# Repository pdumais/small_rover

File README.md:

# A remote controlled vehicle with a mechanical arm using ESP32 and a PS5 Dualsense controller
It's heavy, it's noisy, it's klonky and it looks like a rudimentary machine. That's exactly what I wanted to build.
This is work in progress, so no pictures of the final build yet

# Electronics
I chose to use 2 ESP32. It would have been easier to use just one, but I needed the memory of a esp32-s3 and the classic BT from the ESP32. So I'm using both. 
The ESP32 is the DualSense (PS5 controller) receiver. It handles the connection and incoming data from the Dualsense
and sends it on the i2c bus. This device will most probably end up handling other misc stuff too.

The esp32-s3 is main controller.
    - Controls the 4 motors
    - Controls servo for steering
    - Reads pulse count for each motors (RPM reading)
    - Controls the buzzer
    - Controls LED ring
  
# Choice of motors
I'm using 4 12v DC motors with a stall current of 7A with 4 DRV8871 that limits current to 2A for each motor.
The PWM signal to control the motor is shared for all DRV8871 so 4WD is disabled by software. Emiting the PWM on 3 more pins 
and requiring the motors would enable 4WD.

I tried to do the maths for calculating how big of a motor I would need to make something from steel, so targeting 5kgs.
Every number I came with gave me way too big requirements for motor size. This didn't make any sense considering the current offer of motors. So I decided to aim 251RPM and get high torque. 50$ a motor sounded like expensive so I guess it's good.
It turns out the torque is sufficient since the drv8871 doesn't seem to suffer. But 251RPM is faster than what I need. I would half that if I have to buy new motors.

After shopping around, it seems like building something that requires more than 10A of total current draw would be a different game. Different manufacturer and different tutorials. This hinted me that I should stick to this limit.

# PS5 Controller
I found an ESP32 ps5 library at https://github.com/rodneybakiskan/ps5-esp32.git but it was made for Arduino and is not maintained.
So I modified it to make it work outside the Arduino environment with only ESP-IDF. I'm having problems with it though. 
Connecting the controller is a hit or miss, sometimes I have to reboot the board and retry many times. But it works fine when 
using the Arduino version. I suspect it has something to do with multithreading/multicore since there seems to be a race condition when the controller tries to connect to the board and the board tries to connect to the controller at the same time. So I disabled the connection attempt from the board and it now works. I'll have to make a better fix later.

The controller is a bluetooth device so it has a range limit of 10m, but that's not an issue since I only plan on using this in the house.

# Frame
I chose to use steel for the frame. Aluminum would be better, but I don't have the tools to work aluminum. Plus, aluminum is expensive.
I developed an interest in welding lately so I wanted to play around with my tools.

## Motor mounts
The motor mounting brackets were a bit of a challenge for me. I used a piece of paper and poke holes where the screw holes of them motor were. Then I glued the the paper on a sheet of metal and cut/drilled it.

Of course the first piece I built was bad, but the second one only has 1 hole misaligned. Close enough.
So I now use that piece as a template to build more.

## Subframe
The subframe is just a 3cm wide steel bar welded on the rear axle and bolted on the from one. I prefered to put bolts on the front s o it would be easier to put a better steering mechanism in place some time.

The vehicle is separated in 4 sections: The steering, battery mount, main board and mechanical arm.
There is a series of holes on the subframe that allows me to bolt the battery mount and main board at varying distances.

# Steering
To build a steering, I practiced a few prototypes with Legos. Then I ended up building something like this:
It's not perfect, but it works. Using ball joints would be much better.

# Battery mount
The battery mount is just an L-shape plate on which the battery is tie-wrapped.
The battery sits on a foam to reduce vibrations.

# Main board
The main board is a piece of plywood on which all PCBs are screwed. It consists of the main ESP32 board, the PS5 controller ESP32 board and 2 small 5v regulators.

** Update march 1st.
I created a PCB design to make things a bit more cleaner. I dit not receive the board from the fab yet, but I'm planning on replacing the protoboard with this one

** Update April 2nd.

I finally got the board mounted on the robot.  As with all boards I make, there are a few design flaws on this one. But nothing that can't be fixed. The first issue is that I didn't think about the fact the motors on the right side would need to turn the opposite way from the ones on the left side. So I should've reverse the ouput lines comming from the motor driver for those. The fix was to simply reverse the pins on the motor connectors.

The 2nd flaw is that the 3 signal lines going to the servos for the laser and the sonar are running right above the motor output lines. So when I start the motors, it creates noise on the signal lines and the servos are going crazy. The fix for this was to add a 1k resistor inline on the signal cables. I'm not sure if that's the right fix, but it does work. It's nice to see how the noise being introduced is proportional to the current being used by the motors. For example, noise only happens what starting the motors or stopping them. I understand how electromagnectic induction works, but I didn't think it would be this sensitive.

# Mechanical Arm
The goal was to be able to lift a 500ml can of beer.

- Base
    - Sits on bearing. Base is a big gear but not 360. Like the chute of a snoblower
    - regular DC motor with gear to spin the base. 
        - No need for high torque. No need for high speed although the gear ratio of the base must be taken in consideration

- Boom and Arm
    - 2 regular motors. Or servos? Servos cant be controlled like a real bakhoe
    - Sitting on the base. Pulling the boom and arm using levers
- Grapple
    - Servo sitting on the arm

I wanted the feel of the arm to be like a backhoe control. My initial implementation was taking a value from the Dualsense constroller sticks. This value is between -128 and 127 and was mapped to an angle on the betwwen 0 and 90 on the servo.
This has the affect of using the controller to bring the arm to a set value instead of simply accellerating the arm, like a hydraulic system would. This is a big difference in feel. Also, when releasing the DualSense stick, the servo would return back to its original position. In a hydraulic system, you simply want the arm to stop moving and stay at its current position.

It took a fair amount of code to replicate this behaviour but I'm overall satisfied. It definitely feels more "mechanic" that fluid like a hydraulic system but I think I like it.

The arm can only be used while in "arm" mode. Arm mode is activated/deactivated with the Dualsense cross button.
While in arm mode, the throttle is disabled and the steering is disable to be able to use the sticks for controlling the arm.
Another reason, is that it would require too much power to run the 4 motors and the servos at the same time.
To reduce power usage event more, only 1 servo per sticks can be used at the same time. The 5v regulator that feeds the servo cannot exceed 3A.

# Telemetry
The machine creates a WAP and has the IP address 192.168.4.1. It sends telemetry data over a websocket every second. This packet
contains the metrics of the machine as defined in [mainboard/main/common.h](mainboard//main/common.h) in `struct metrics_t`. There is web page served on port 80 to render the raw data into a user friendly view.
<p style="text-align: center;"> 

# Wifi
The vehicle creates a WAP called "ROVER". I've configured my router to auto-connect to that WAP and take the address 192.168.4.2.
The router then forwards UDP 242 to my dev machine so I can receive stats broadcast while developing.

From my dev machine, I can also trigger a OTA firmware upgrade so I don't need to connect the vehicle with a USB cable anymore.

# Recording
The vehicle can learn routes by recording user inputs while controlling with the dualsense.
The Circle button enters the machine into recording mode. It starts recording all throttle changes and steering angle changes as the user operates the machine. Pressing the triangle button replays a recording. 

By replaying the same throttle values and steering angle at the same time deltas, the machine should be able to replicate the same path that was recorded but it needs to be placed at the same starting position than the recording was made at.

I was initially thinking of using a digital magnetometer but I don't think it would give me
much more precision than what I currently get. A GPS would be great, but won't work indoor and the accuracy would be lower (1.5m margin of error I believe).

In practice, the replay is not 100% accurate because I suspect that the tires slip on the floor in a different way each time. There is also a margin of error in the timing. The results are quite good still, but the machine doesn't come back exactly where it was all the time, but quite close.

The record buffer is a bit small too. It can hold up to 300 events and then recording stops. I am planning on flushing the buffer to flash when it is full and be able to record at least 1000 events.

# Improvements
There are many design flaws with this machine. Mostly because of my limited knowledge about mechanics and electronics, but also because
of a consious choice to sacrifice performance to be able to use limited resources. For example, a few pivot points would gain by being installed on a bearing or ball joint, but this would have become too expensive. I had everything on hand already to build a poorman's version. I like to think of it as working as if in a post-apocalyptic world and scavanging for parts :)

# Pictures

Project status Jan 17

Guts and wheels mounted

Project status Jan 22

Prototype is working. I'm ready to finish the frame. So it's now time to disassemble everything.

Everything is painted. I just need to let it dry 24h and I will re-assemble everything

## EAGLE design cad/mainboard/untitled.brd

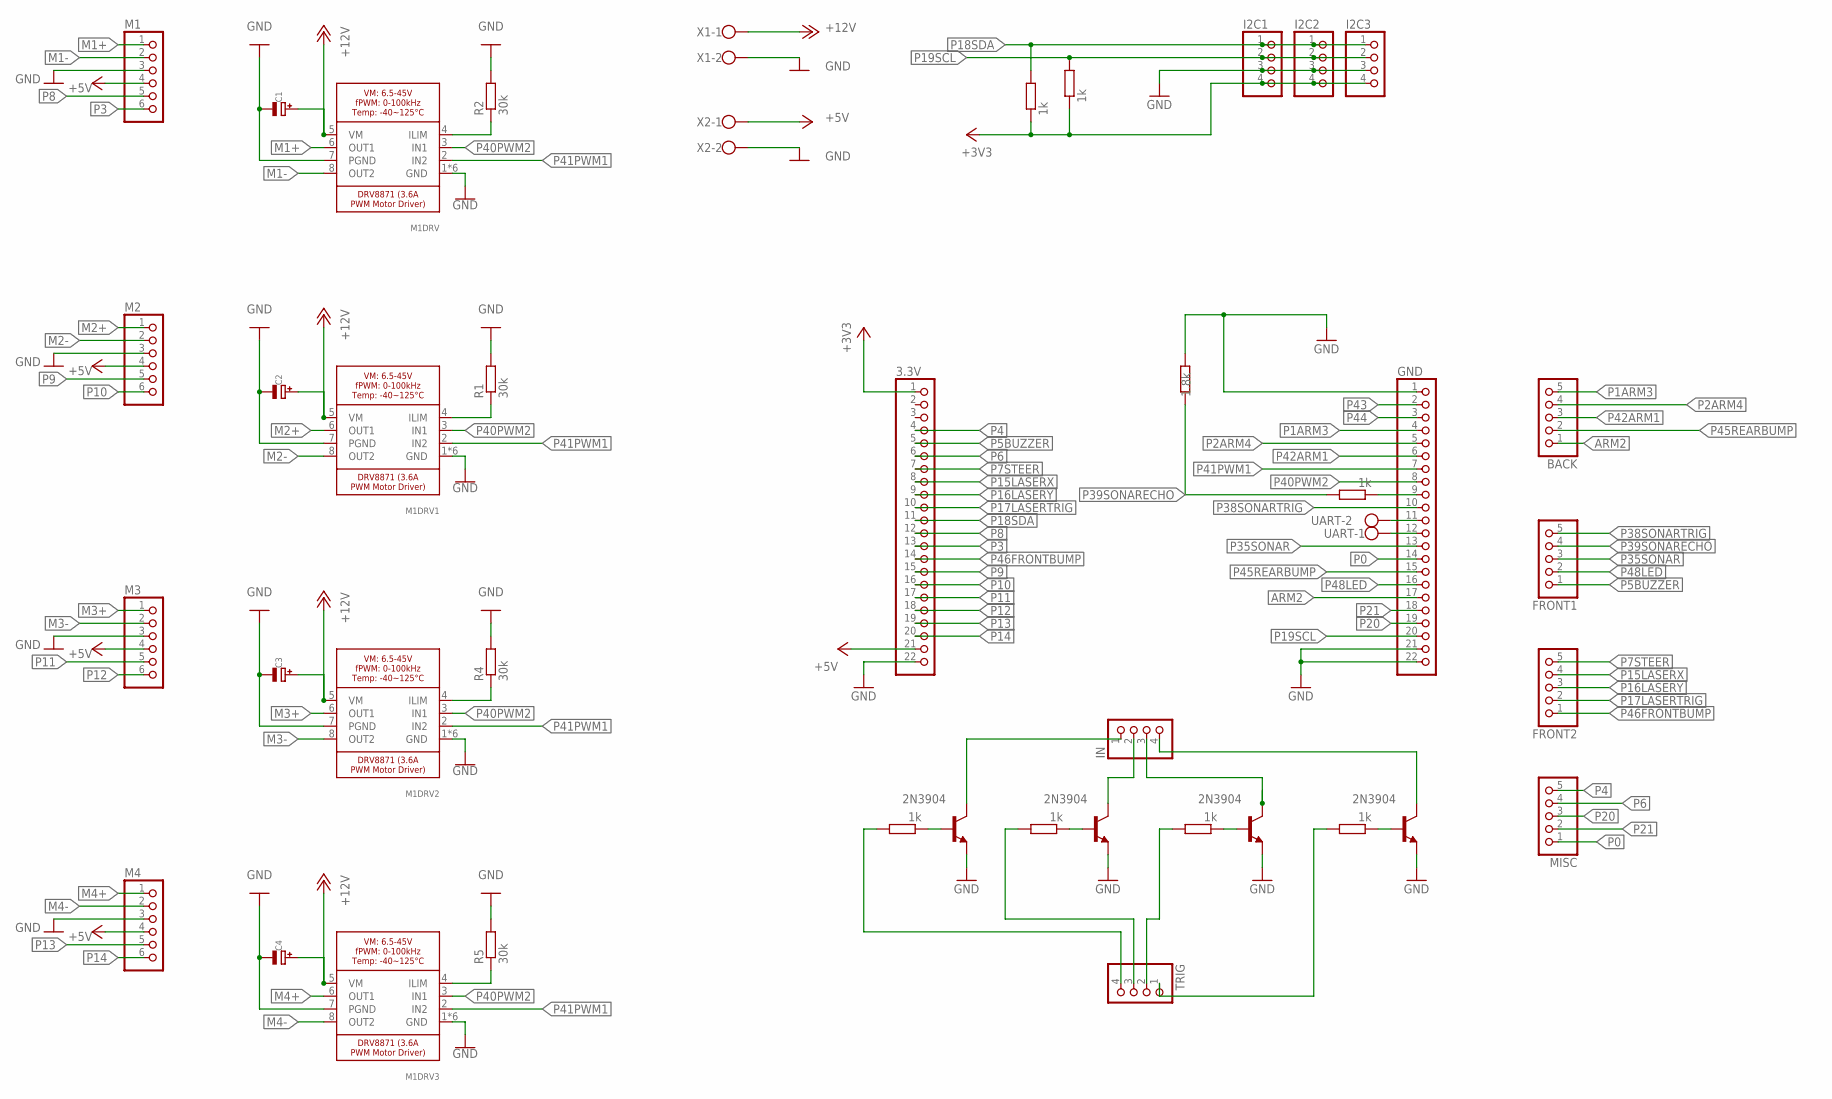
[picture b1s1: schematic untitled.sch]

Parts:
1K, 1K1, 1K3, 1K4, 1K5, 1K6: 1k; 0207/10
1K2: 1.8k; 0207/10
3.3V: PINHD-1X22; 1X22
BACK: PINHD-1X5; 1X05
C1, C2, C3, C4: MICROBUILDER_CAP_ELECTROLYTICPTH_3.5MMGRID_10MMDIA; MICROBUILDER_CELEC_3.5MM_10MM
FRONT1, FRONT2: PINHD-1X5; 1X05
GND: PINHD-1X22; 1X22
I2C1, I2C2, I2C3: PINHD-1X4; 1X04
IN: PINHD-1X4; 1X04
M1, M2, M3, M4: PINHD-1X6; 1X06
M1DRV, M1DRV1, M1DRV2, M1DRV3: MICROBUILDER_DRV8871; MICROBUILDER_HSOP8
MISC: PINHD-1X5; 1X05
R1, R2, R4, R5: 30k; 0207/10
R3: 1k; 0207/10
T1, T2, T3, T4: 2N3904; TO92
TRIG: PINHD-1X4; 1X04
UART: W237-102
X1, X2: W237-102

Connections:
+3V3: 1K.1, 3.3V.1, I2C1.4, I2C2.4, I2C3.4, R3.1
+5V: 3.3V.21, M1.4, M2.4, M3.4, M4.4, X2.1
+12V: C1.+, C2.+, C3.+, C4.+, M1DRV.5 (VM), M1DRV1.5 (VM), M1DRV2.5 (VM), M1DRV3.5 (VM), X1.1
ARM2: BACK.1, GND.17
GND: 1K2.1, 3.3V.22, C1.-, C2.-, C3.-, C4.-, GND.1, GND.21, GND.22, I2C1.3, I2C2.3, I2C3.3, M1.3, M1DRV.1 (GND), M1DRV.7 (PGND), M1DRV.GND, M1DRV.P$1 (GND), M1DRV.P$2 (GND), M1DRV.P$3 (GND), M1DRV.P$4 (GND), M1DRV1.1 (GND), M1DRV1.7 (PGND), M1DRV1.GND, M1DRV1.P$1 (GND), M1DRV1.P$2 (GND), M1DRV1.P$3 (GND), M1DRV1.P$4 (GND), M1DRV2.1 (GND), M1DRV2.7 (PGND), M1DRV2.GND, M1DRV2.P$1 (GND), M1DRV2.P$2 (GND), M1DRV2.P$3 (GND), M1DRV2.P$4 (GND), M1DRV3.1 (GND), M1DRV3.7 (PGND), M1DRV3.GND, M1DRV3.P$1 (GND), M1DRV3.P$2 (GND), M1DRV3.P$3 (GND), M1DRV3.P$4 (GND), M2.3, M3.3, M4.3, R1.2, R2.2, R4.2, R5.2, T1.3 (E), T2.3 (E), T3.3 (E), T4.3 (E), X1.2, X2.2
IN: IN.1, T4.1 (C)
M1+: M1.1, M1DRV.6 (OUT1)
M1-: M1.2, M1DRV.8 (OUT2)
M2+: M1DRV1.6 (OUT1), M2.1
M2-: M1DRV1.8 (OUT2), M2.2
M3+: M1DRV2.6 (OUT1), M3.1
M3-: M1DRV2.8 (OUT2), M3.2
M4+: M1DRV3.6 (OUT1), M4.1
M4-: M1DRV3.8 (OUT2), M4.2
unnamed: M1DRV1.4 (ILIM), R1.1
unnamed: M1DRV2.4 (ILIM), R4.1
unnamed: 1K1.1, GND.9
unnamed: M1DRV3.4 (ILIM), R5.1
unnamed: GND.11, UART.2
unnamed: GND.12, UART.1
unnamed: IN.2, T1.1 (C)
unnamed: 1K3.1, T1.2 (B)
unnamed: M1DRV.4 (ILIM), R2.1
unnamed: 1K3.2, TRIG.3
unnamed: IN.3, T2.1 (C)
unnamed: 1K4.1, T2.2 (B)
unnamed: 1K4.2, TRIG.2
unnamed: IN.4, T3.1 (C)
unnamed: 1K5.1, T3.2 (B)
unnamed: 1K5.2, TRIG.1
unnamed: 1K6.1, T4.2 (B)
unnamed: 1K6.2, TRIG.4
P0: GND.14, MISC.1
P1ARM3: BACK.5, GND.4
P2ARM4: BACK.4, GND.5
P3: 3.3V.13, M1.6
P4: 3.3V.4, MISC.5
P5BUZZER: 3.3V.5, FRONT1.1
P6: 3.3V.6, MISC.4
P7STEER: 3.3V.7, FRONT2.5
P8: 3.3V.12, M1.5
P9: 3.3V.15, M2.5
P10: 3.3V.16, M2.6
P11: 3.3V.17, M3.5
P12: 3.3V.18, M3.6
P13: 3.3V.19, M4.5
P14: 3.3V.20, M4.6
P15LASERX: 3.3V.8, FRONT2.4
P16LASERY: 3.3V.9, FRONT2.3
P17LASERTRIG: 3.3V.10, FRONT2.2
P18SDA: 1K.2, 3.3V.11, I2C1.1, I2C2.1, I2C3.1
P19SCL: GND.20, I2C1.2, I2C2.2, I2C3.2, R3.2
P20: GND.19, MISC.3
P21: GND.18, MISC.2
P35SONAR: FRONT1.3, GND.13
P38SONARTRIG: FRONT1.5, GND.10
P39SONARECHO: 1K1.2, 1K2.2, FRONT1.4
P40PWM2: GND.8, M1DRV.3 (IN1), M1DRV1.3 (IN1), M1DRV2.3 (IN1), M1DRV3.3 (IN1)
P41PWM1: GND.7, M1DRV.2 (IN2), M1DRV1.2 (IN2), M1DRV2.2 (IN2), M1DRV3.2 (IN2)
P42ARM1: BACK.3, GND.6
P43: GND.2
P44: GND.3
P45REARBUMP: BACK.2, GND.15
P46FRONTBUMP: 3.3V.14, FRONT2.1
P48LED: FRONT1.2, GND.16

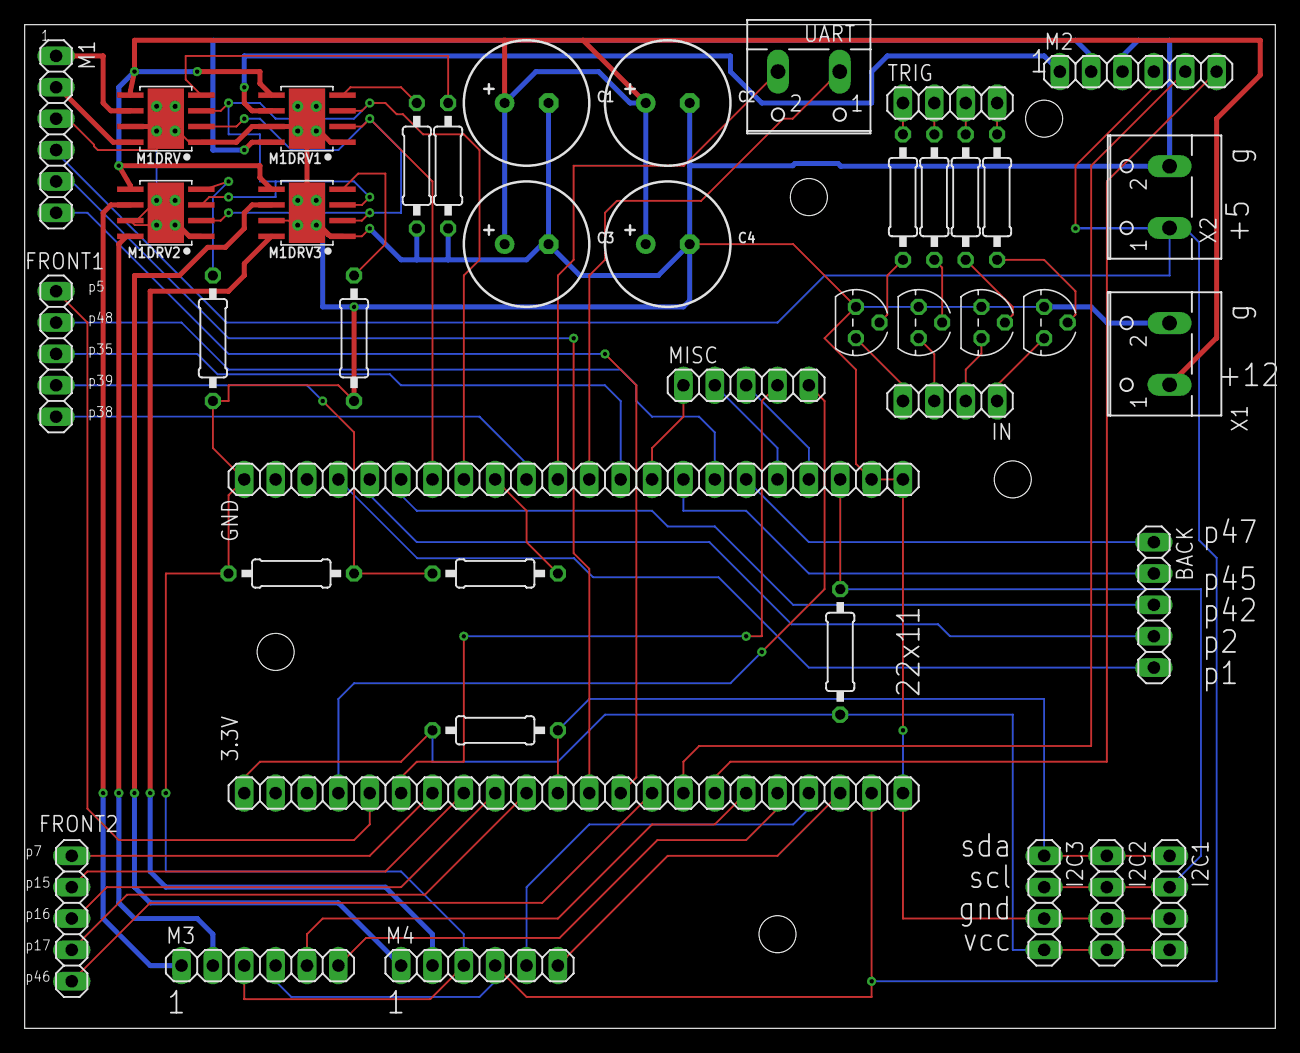
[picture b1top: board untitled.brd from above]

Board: 2 copper layers, 101.3 x 81.3 mm, 42 parts (0 on the bottom side), 63 nets.

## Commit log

2024-01-09 First
2024-01-24 first
    update
    readme
2024-01-28 arm code
2024-01-29 cleanup
2024-01-30 record-replay
2024-01-31 refactored FSM. Adding BT pairing
2024-02-02 Dualsense works with extended reports and can control rumble and LEDs
2024-02-03 feeback to controller
2024-02-06 Changed i2c to uart
2024-02-11 various improvements
2024-02-15 Collision detection
2024-02-20 telemetry
2024-02-22 sensors
2024-02-22 board
2024-02-26 accelerometer
2024-03-01 magneto
2024-03-01 fixed merge errors
2024-03-01 docs
2024-03-02 battery voltage monitor
2024-03-03 changed buzzer to use ledc
2024-03-03 melody on honk
2024-03-03 update notes

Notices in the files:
parts and their libraries:
SparkFun-PowerSymbols: Licensing: Creative Commons ShareAlike 4.0 International - https://creativecommons.org/licenses/by-sa/4.0
